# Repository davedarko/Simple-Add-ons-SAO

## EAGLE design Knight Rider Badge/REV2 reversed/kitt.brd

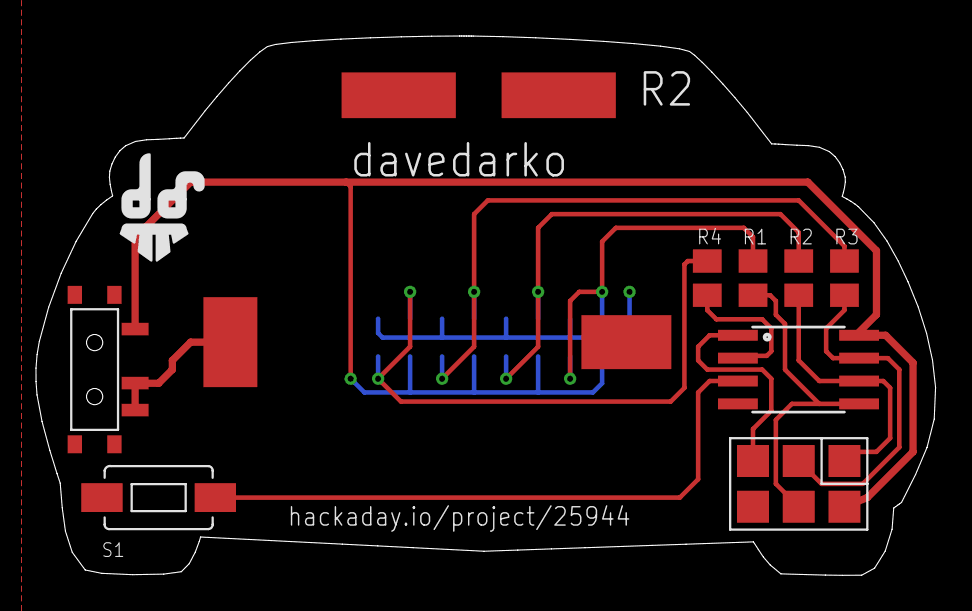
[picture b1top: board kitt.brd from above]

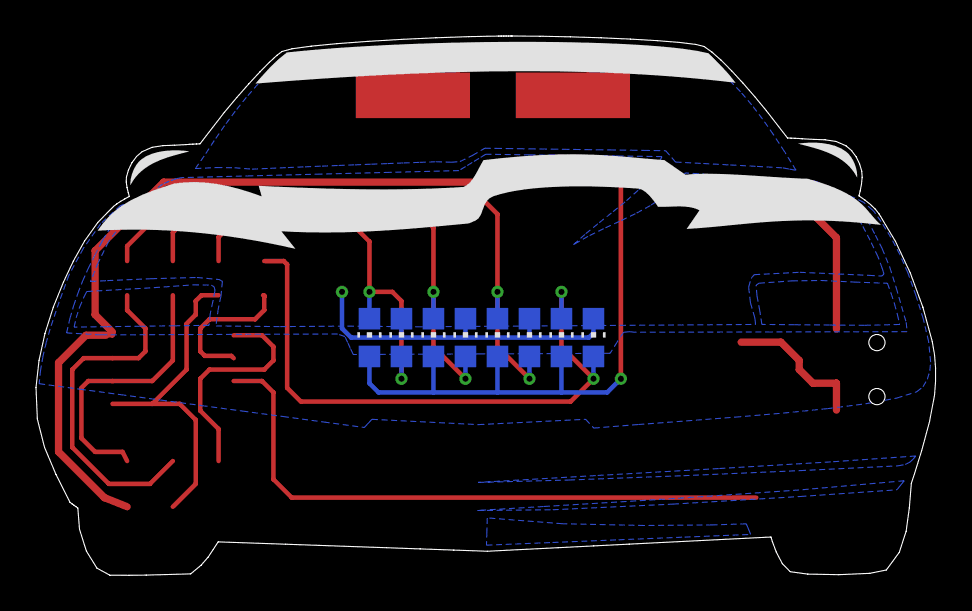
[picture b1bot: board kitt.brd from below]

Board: 2 copper layers, 50.0 x 30.0 mm, 18 parts (8 on the bottom side), 13 nets.

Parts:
JP1: AVR_SPI_PRG_6; 2X3_SMD_PAD
LED1, LED2, LED3, LED4, LED5, LED6, LED7, LED8: RED; CHIP-LED0805
R1, R2, R3, R4: 150R; M0805
S1: SWITCH-MOMENTARY-2-SMD-1101NE; TACTILE-SWITCH-1101NE
U1: Tiny85-20-SMT; SO08-EIAJ
U$1: SWITCH_SPDT; KPS-1290
U$2: CR2032SMD
U$3: DAVEDARKO2_LOGO

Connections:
GND: JP1.P$6, LED2.C, LED4.C, LED6.C, LED8.C, S1.P$2, U1.4, U$2.-
MISO: JP1.P$1, R2.1, U1.6
MOSI: JP1.P$4, R1.1, U1.5
unnamed: S1.P$1, U1.3
unnamed: LED1.C, LED2.A, R1.2
unnamed: U$1.P, U$1.S, U$2.+
unnamed: LED3.C, LED4.A, R2.2
unnamed: LED5.C, LED6.A, R3.2
unnamed: LED7.C, LED8.A, R4.2
PB3: R4.1, U1.2
RST: JP1.P$5, U1.1
SCK: JP1.P$3, R3.1, U1.7
VCC: JP1.P$2, LED1.A, LED3.A, LED5.A, LED7.A, U1.8, U$1.O

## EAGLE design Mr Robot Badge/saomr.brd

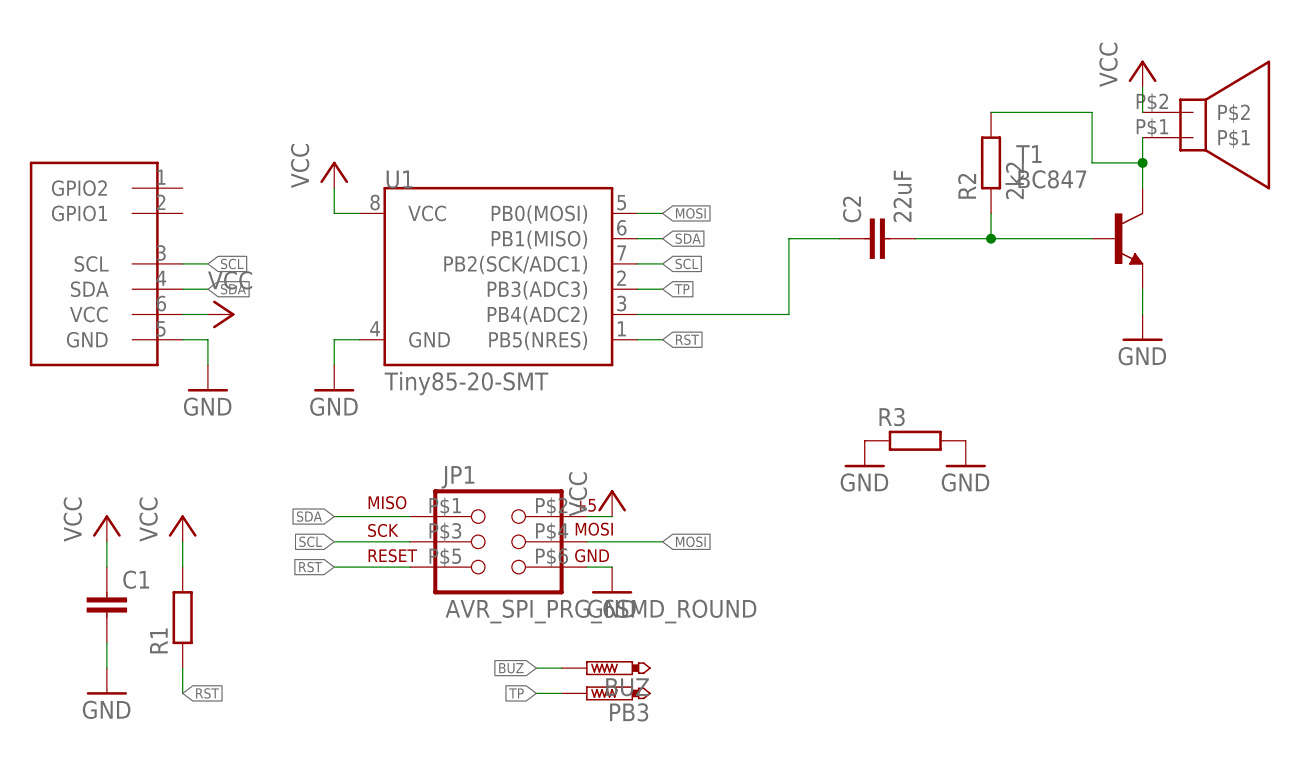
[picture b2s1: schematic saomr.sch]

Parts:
BUZ: PTR1B2,54; B2,54
C1: C-EUC1206; C1206
C2: 22uF; C1206
JP1: AVR_SPI_PRG_6SMD_ROUND; 2X3_SMD_PAD_ROUND
PB3: PTR1B2,54; B2,54
R1: R-EU_R1206; R1206
R2: 2k2; R1206
R3: R-EU_M1206; M1206
T1: BC847; SOT23
U1: Tiny85-20-SMT; SO08-EIAJ
U$1: SPEAKERKMTG-1102; KMTG-1102
U$2: SAO-SHITTY-ADDON; 2X3_SMD

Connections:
BUZ: BUZ.TP, C2.1, U1.3 (PB4(ADC2))
GND: C1.2, JP1.P$6 (6), R3.1, R3.2, T1.2 (E), U1.4 (GND), U$2.5 (GND)
MOSI: JP1.P$4 (4), U1.5 (PB0(MOSI))
unnamed: C2.2, R2.1, T1.1 (B)
unnamed: R2.2, T1.3 (C), U$1.P$1
RST: JP1.P$5 (5), R1.1, U1.1 (PB5(NRES))
SCL: JP1.P$3 (3), U1.7 (PB2(SCK/ADC1)), U$2.3 (SCL)
SDA: JP1.P$1 (1), U1.6 (PB1(MISO)), U$2.4 (SDA)
TP: PB3.TP, U1.2 (PB3(ADC3))
VCC: C1.1, JP1.P$2 (2), R1.2, U1.8 (VCC), U$1.P$2, U$2.6 (VCC)

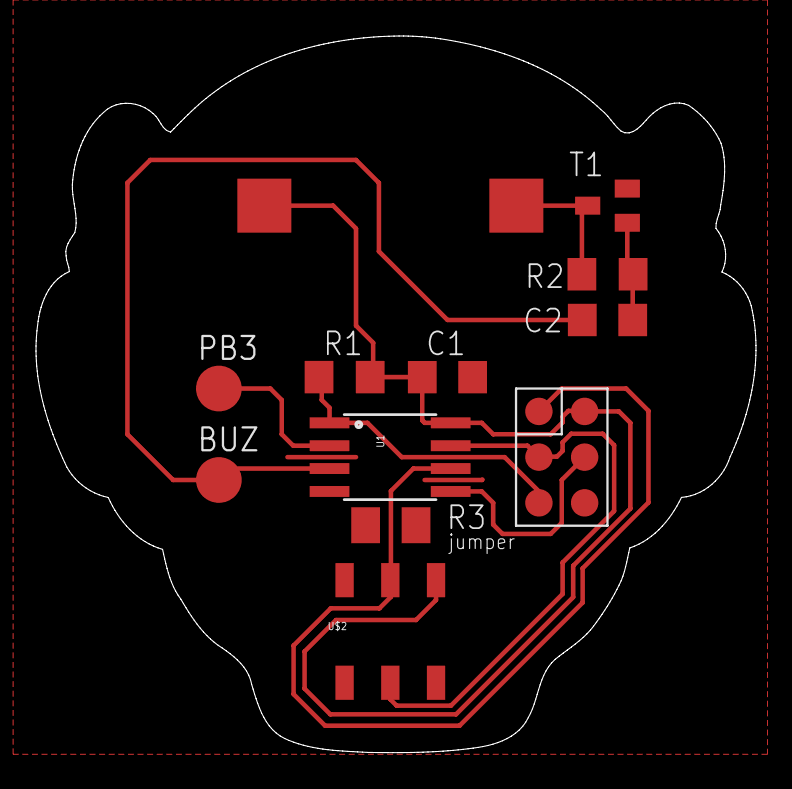
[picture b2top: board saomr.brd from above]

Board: 2 copper layers, 40.0 x 39.8 mm, 13 parts (0 on the bottom side), 10 nets.

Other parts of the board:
U$3: DAVEDARKO_GOLD

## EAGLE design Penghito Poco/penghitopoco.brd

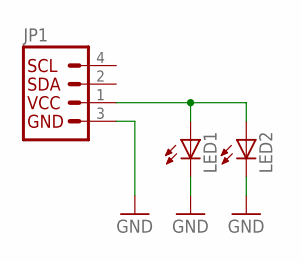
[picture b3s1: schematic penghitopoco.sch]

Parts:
JP1: I2C_STANDARDI2C_SAO; 2X2
LED1, LED2: LED5MM

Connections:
GND: JP1.3 (GND), LED1.K (C), LED2.K (C)
unnamed: JP1.1 (VCC), LED1.A, LED2.A

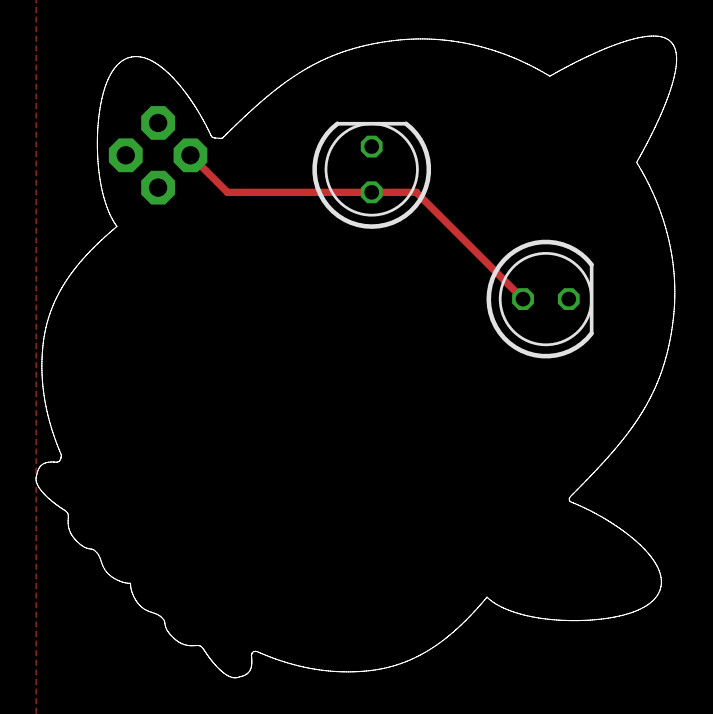
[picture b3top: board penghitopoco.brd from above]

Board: 2 copper layers, 35.6 x 35.7 mm, 3 parts (1 on the bottom side), 2 nets.

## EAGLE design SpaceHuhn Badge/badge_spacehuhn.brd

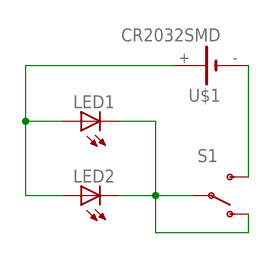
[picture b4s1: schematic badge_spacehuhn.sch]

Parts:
LED1, LED2: LED5MM
S1: SWITCH-SPDT-SMD-A; SWITCH-SPST-SMD-A
U$1: CR2032SMD

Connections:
GND: LED1.K (C), LED2.K (C), S1.1 (O), S1.2
unnamed: S1.3 (S), U$1.-
VCC: LED1.A, LED2.A, U$1.+

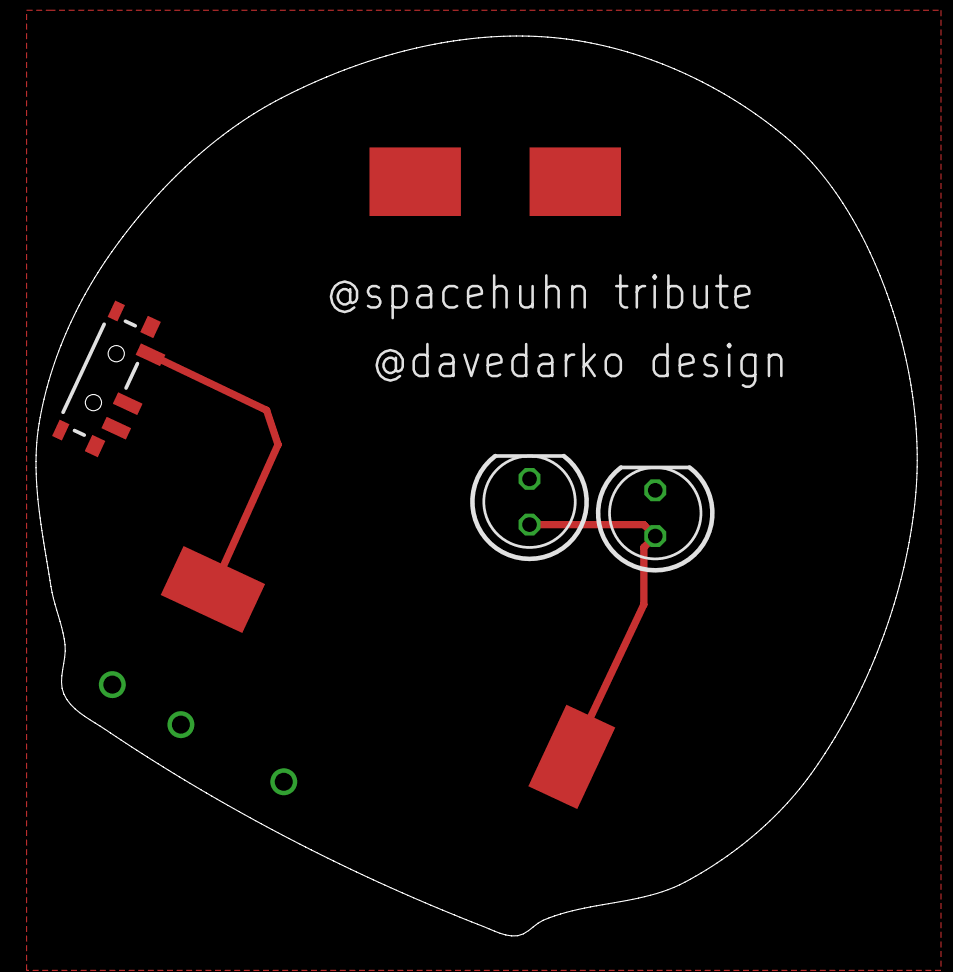
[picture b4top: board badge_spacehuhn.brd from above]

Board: 2 copper layers, 49.0 x 50.0 mm, 5 parts (0 on the bottom side), 3 nets.

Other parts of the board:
U$2: DAVEDARKO_GOLD

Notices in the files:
parts and their libraries:
SparkFun-DigitalIC: Licensing: Creative Commons ShareAlike 4.0 International - https://creativecommons.org/licenses/by-sa/4.0
